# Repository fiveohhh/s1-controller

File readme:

Raspberry Pi based controller for a La Spaziale Vivaldi s1

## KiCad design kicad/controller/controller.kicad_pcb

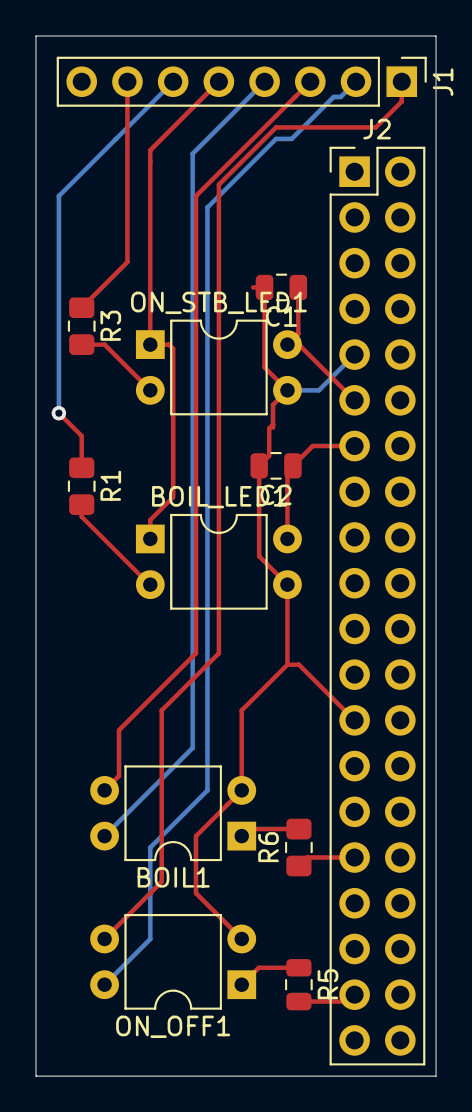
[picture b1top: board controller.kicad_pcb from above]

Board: 2 copper layers, 22.2 x 57.8 mm, 12 parts (0 on the bottom side), 16 nets.

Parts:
BOIL1: PC817; DIP-4_W7.62mm
BOIL_LED1: PC817; DIP-4_W7.62mm
C1, C2: C; C_0805_2012Metric
J1: Screw_Terminal_01x08; PinHeader_1x08_P2.54mm_Vertical
J2: Raspberry_Pi_2_3; PinHeader_2x20_P2.54mm_Vertical
ON_OFF1: PC817; DIP-4_W7.62mm
ON_STB_LED1: PC817; DIP-4_W7.62mm
R1, R3, R6: R_US; R_0805_2012Metric_Pad1.15x1.40mm_HandSolder
R5: R_US; R_0805_2012Metric

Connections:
GND: BOIL1.2, BOIL_LED1.3, C1.2, C2.2, J2.9, J2.25, ON_OFF1.2, ON_STB_LED1.3
unnamed: BOIL1.1, R6.2
unnamed: BOIL1.3, J1.3
unnamed: BOIL1.4, J1.4
unnamed: BOIL_LED1.1, J1.5, ON_STB_LED1.1
unnamed: BOIL_LED1.2, R1.2
unnamed: BOIL_LED1.4, C2.1, J2.13
unnamed: C1.1, J2.11, ON_STB_LED1.4
unnamed: J1.1, ON_OFF1.3
unnamed: J1.2, ON_OFF1.4
unnamed: J1.6, R1.1
unnamed: J1.7, R3.1
unnamed: J2.31, R6.1
unnamed: J2.37, R5.2
unnamed: ON_OFF1.1, R5.1
unnamed: ON_STB_LED1.2, R3.2

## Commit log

2018-12-13 Initial add of board files
2018-12-13 Initial add of s1.py
2018-12-27 Initial working version
2018-12-27 now better
2018-12-27 Working version of web server
2018-12-27 Removing button readers
    Not much point in reading the button 2 and needed button 2 wire for a wire I missed the first time
2018-12-27 Improving logs
2018-12-27 More logging updates
2018-12-27 formatting cleanup
2018-12-27 More og fixes
2018-12-27 Another log update
2018-12-31 Adding auto off ability
2018-12-31 better err handling
2018-12-31 Allowing boiler set from api
2018-12-31 Adding boiler on logic
2019-01-01 attempt to fix double logging
    sytax fix too
2019-01-01 Lowering sampling history to 10
    The leds turn on and off in about .5 seconds. So 1 second should be
    enough to get a sampling history
2019-01-01 Adding steam boiler cycles/runtime logic
2019-01-01 fixing boiler on time calc
2019-01-01 Changing server to be single threaded and updating boiler logic
2019-01-01 Fixing bug
2019-01-01 Adding firestore logging
2019-01-01 rounding off seconds and also reporting as minutes
2019-01-01 Fixing minute conversion
2019-01-04 Adding timezone
2019-01-04 Adding cloud logging
2019-01-05 Improving error handling
2019-01-05 Updating net and gerber files
2019-01-05 Updating pcb file
2019-01-05 Changind firebase collection name to logs
    When it was log it seemed to cause some issue in firebase.
